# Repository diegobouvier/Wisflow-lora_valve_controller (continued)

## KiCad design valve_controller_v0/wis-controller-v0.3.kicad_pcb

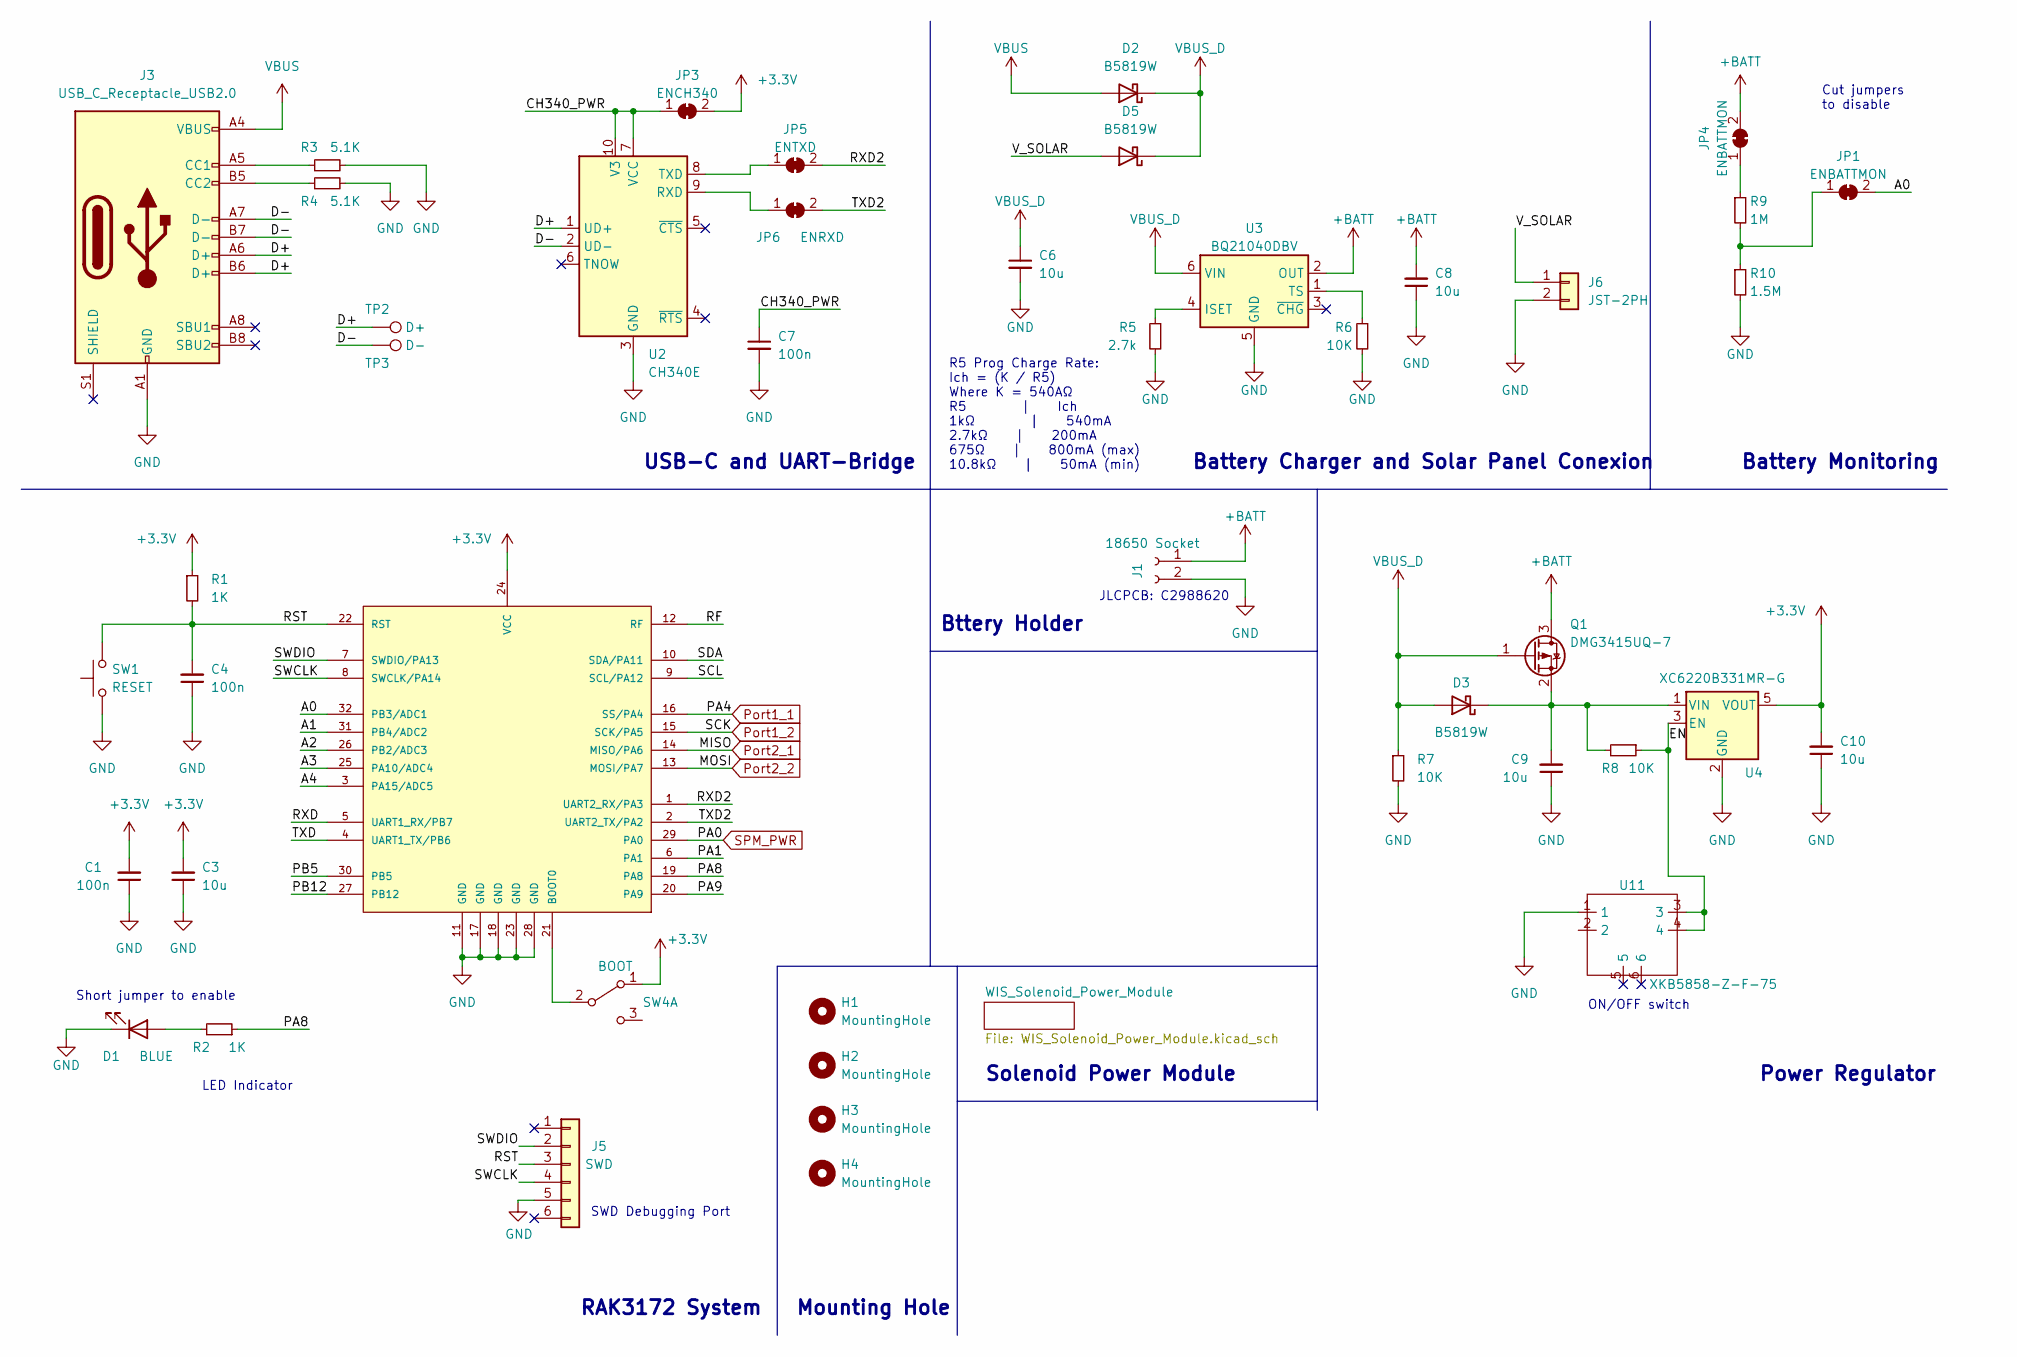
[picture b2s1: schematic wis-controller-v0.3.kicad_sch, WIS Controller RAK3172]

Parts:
C1, C4, C7: 100n; C_0603_1608Metric; Part Description Ceramic Capacitor 100nF 10% 10V X7R
C3, C6: 10u; C_0603_1608Metric; Part Description Ceramic Capacitor 10uF 10% 10V X5R
C8, C9, C10: 10u; C_0805_2012Metric; Part Description Ceramic Capacitor 10uF 10% 10V X5R
D1: BLUE; LED_0603_1608Metric; Part Description Blue 2V 25mA
D2, D5: B5819W; D_SOD-123
D3: B5819W; D_SOD-123; Part Description 0.05mA@40V 0.58V@1A
H1, H2, H3, H4: MountingHole; MountingHole_2.5mm
J1: 18650 Socket; BatteryHolder_MPD_BK-18650-PC2
J3: USB_C_Receptacle_USB2.0; USB_C_Receptacle_XKB_U262-16XN-4BVC11; Part Number U262-161N-4BVC11
J5: SWD; Tag-Connect_TC2030-IDC-NL_2x03_P1.27mm_Vertical
J6: JST-2PH; JST_PH_S2B-PH-SM4-TB_1x02-1MP_P2.00mm_Horizontal; Part Number JST-PH S2B-PH-SM4-TB
JP1, JP4: ENBATTMON; SolderJumper-2_P1.3mm_Bridged_RoundedPad1.0x1.5mm
JP3: ENCH340; SolderJumper-2_P1.3mm_Bridged_RoundedPad1.0x1.5mm
JP5: ENTXD; SolderJumper-2_P1.3mm_Bridged_RoundedPad1.0x1.5mm
JP6: ENRXD; SolderJumper-2_P1.3mm_Bridged_RoundedPad1.0x1.5mm
Q1: DMG3415UQ-7; SOT-23; Part Number DMG3415UQ-7
R1, R2: 1K; R_0603_1608Metric; Part Description Resistor 1k 5% 100mW
R3, R4: 5.1K; R_0603_1608Metric; Part Description Resistor 5.1K 1% 100mW
R5: 2.7k; R_0603_1608Metric; Part Description Resistor 5.1k 1% 100mW
R6, R7, R8: 10K; R_0603_1608Metric; Part Description Resistor 10k 5% 100mW
R9: 1M; R_0603_1608Metric; Part Description Resistor 4.7M 1% 100mW
R10: 1.5M; R_0603_1608Metric; Part Description Resistor 10M 1% 100mW
SW1: RESET; SW_SPST_B3U-1000P; Part Number B3U-1000P
SW4: BOOT; Slide_switch
TP2: D+; TestPoint_Pad_D1.0mm
TP3: D-; TestPoint_Pad_D1.0mm
U1: RAK3172; Part Number RAK3172
U2: CH340E; MSOP-10_3x3mm_P0.5mm; Part Number CH340E
U3: BQ21040DBV; SOT-23-6
U4: XC6220B331MR-G; SOT-23-5; Part Number XC6220B331MR-G
U11: XKB5858-Z-F-75; WIS-Push_Button

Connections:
+3.3V: C1.2, C3.2, C10.2, JP3.2 (B), R1.1, SW4.1 (A), U1.24 (VCC), U4.5 (VOUT); also elsewhere on the board
+BATT: C8.2, J1.1, JP4.2 (B), Q1.3 (D), U3.2 (OUT); also elsewhere on the board
/A0: JP1.2 (B), U1.32 (PB3/ADC1)
/A1: U1.31 (PB4/ADC2)
/A2: U1.26 (PB2/ADC3)
/A3: U1.25 (PA10/ADC4)
/A4: U1.3 (PA15/ADC5)
/CH340_PWR: C7.1, JP3.1 (A), U2.7 (VCC), U2.10 (V3)
/D+: J3.A6 (D+), J3.B6 (D+), TP2.1, U2.1 (UD+)
/D-: J3.A7 (D-), J3.B7 (D-), TP3.1, U2.2 (UD-)
/EN: R8.1, U4.3 (EN), U11.3, U11.4
/PA1: U1.6 (PA1)
/PA8: R2.1, U1.19 (PA8)
/PA9: U1.20 (PA9)
/PB5: U1.30 (PB5)
/PB12: U1.27 (PB12)
/RF: U1.12 (RF)
/RST: C4.2, J5.3, R1.2, SW1.2, U1.22 (RST)
/RXD: U1.5 (UART1_RX/PB7)
/RXD2: JP5.2 (B), U1.1 (UART2_RX/PA3)
/SCL: U1.9 (SCL/PA12)
/SDA: U1.10 (SDA/PA11)
/SWCLK: J5.4, U1.8 (SWCLK/PA14)
/SWDIO: J5.2, U1.7 (SWDIO/PA13)
/TXD: U1.4 (UART1_TX/PB6)
/TXD2: JP6.2 (B), U1.2 (UART2_TX/PA2)
/V_SOLAR: D5.2 (A), J6.1
GND: C1.1, C3.1, C4.1, C6.2, C7.2, C8.1, C9.1, C10.1, D1.1 (K), J1.2, J3.A1 (GND), J3.A12 (GND), J3.B1 (GND), J3.B12 (GND), J5.5, J6.2, R3.2, R4.2, R5.2, R6.2, R7.2, R10.2, SW1.1, U1.11 (GND), U1.17 (GND), U1.18 (GND), U1.23 (GND), U1.28 (GND), U2.3 (GND), U3.5 (GND), U4.2 (GND), U11.1; also elsewhere on the board
unnamed: D1.2 (A), R2.2
unnamed: C9.2, D3.1 (K), Q1.2 (S), R8.2, U4.1 (VIN)
unnamed: J3.A5 (CC1), R3.1
unnamed: J3.B5 (CC2), R4.1
unnamed: JP1.1 (A), R9.2, R10.1
unnamed: JP4.1 (A), R9.1
unnamed: JP5.1 (A), U2.8 (TXD)
unnamed: JP6.1 (A), U2.9 (RXD)
unnamed: SW4.2 (B), U1.21 (BOOT0)
unnamed: R5.1, U3.4 (ISET)
unnamed: R6.1, U3.1 (TS)
Port1_1: U1.16 (SS/PA4); also elsewhere on the board
Port1_2: U1.15 (SCK/PA5); also elsewhere on the board
Port2_1: U1.14 (MISO/PA6); also elsewhere on the board
Port2_2: U1.13 (MOSI/PA7); also elsewhere on the board
SPM_PWR: U1.29 (PA0); also elsewhere on the board
VBUS: D2.2 (A), J3.A4 (VBUS), J3.A9 (VBUS), J3.B4 (VBUS), J3.B9 (VBUS)
VBUS_D: C6.1, D2.1 (K), D3.2 (A), D5.1 (K), Q1.1 (G), R7.1, U3.6 (VIN)

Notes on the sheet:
ON/OFF switch
Battery Monitoring
RAK3172 System
Mounting Hole
R5 Prog Charge Rate: Ich = (K / R5) Where K = 540AΩ R5 | Ich 1kΩ | 540mA 2.7kΩ | 200mA 675Ω | 800mA (max) 10.8kΩ | 50mA (min)
Cut jumpers to disable
JLCPCB: C2988620
Short jumper to enable
USB-C and UART-Bridge
SWD Debugging Port
LED Indicator
Solenoid Power Module
Power Regulator
Battery Charger and Solar Panel Conexion
Bttery Holder

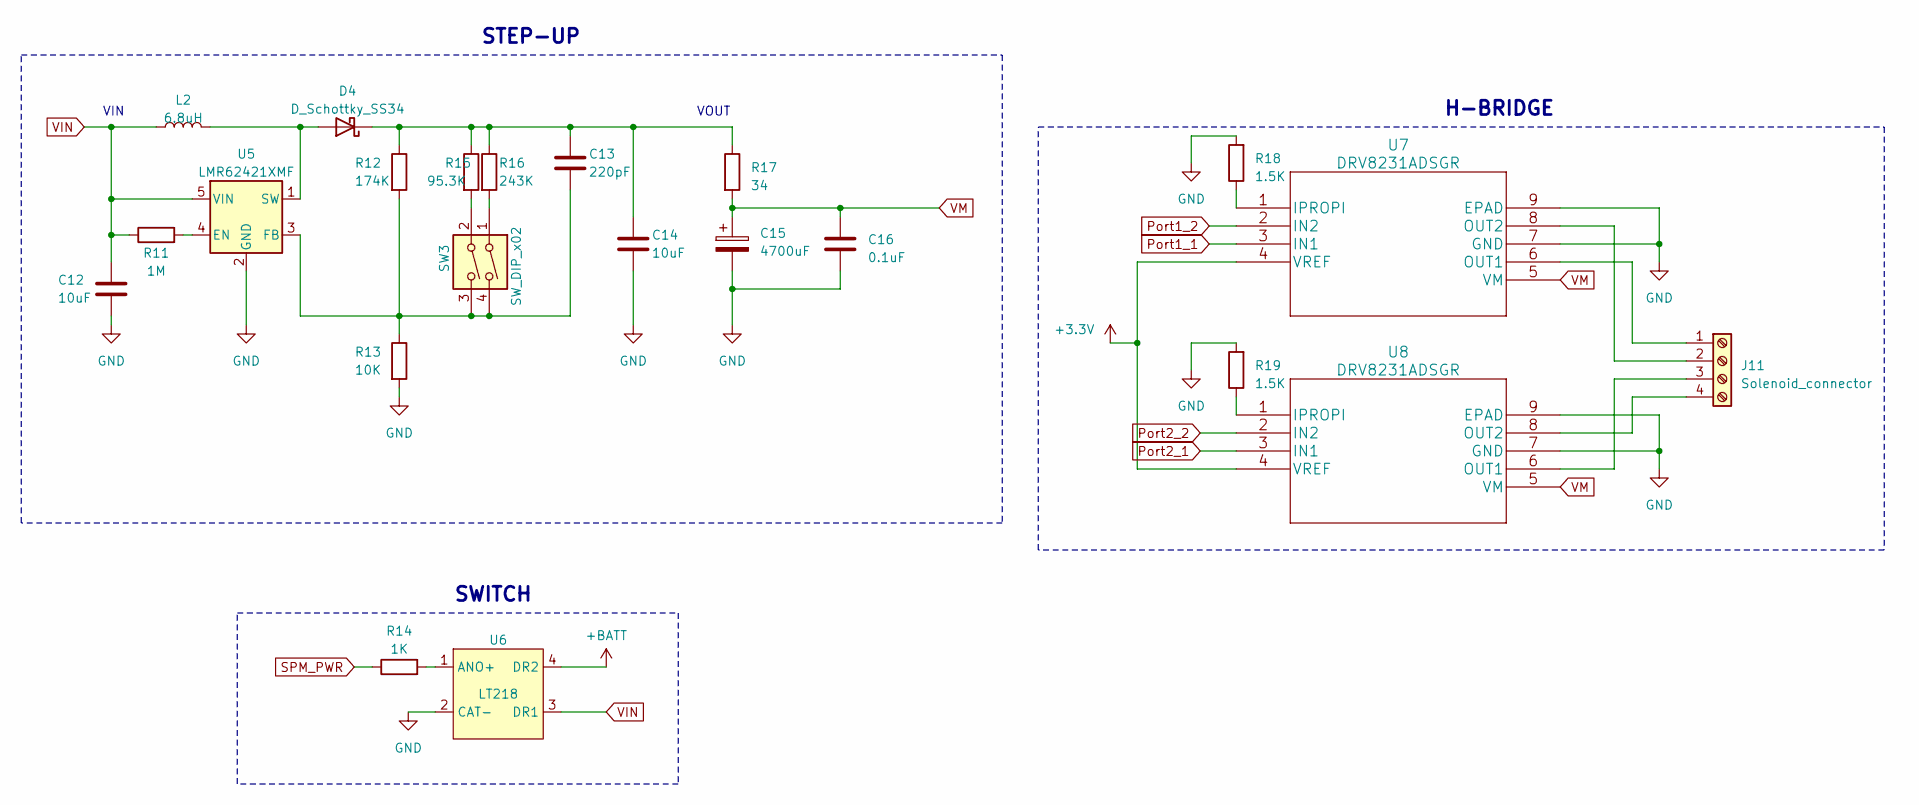
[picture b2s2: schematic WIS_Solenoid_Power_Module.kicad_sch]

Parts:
C12, C14: 10uF; C_0603_1608Metric
C13: 220pF; C_0603_1608Metric
C15: 4700uF; CP_Radial_D16.0mm_P7.50mm
C16: 0.1uF; C_0603_1608Metric
D4: D_Schottky_SS34; Dioide_v1.4
J11: Solenoid_connector; TerminalBlock_bornier-4_P5.08mm
L2: 6.8uH; Inductor_6R8
R11: 1M; R_0603_1608Metric
R12: 174K; R_0603_1608Metric
R13: 10K; R_0603_1608Metric
R14: 1K; R_0603_1608Metric
R15: 95.3K; R_0603_1608Metric
R16: 243K; R_0603_1608Metric
R17: 34; R_2512_6332Metric
R18, R19: 1.5K; R_0603_1608Metric
SW3: SW_DIP_x02; WIS_DIP_Switch
U5: LMR62421XMF; SOT-23-5
U6: LT218; SOP-4
U7, U8: DRV8231ADSGR

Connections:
+3.3V: U7.4 (VREF), U8.4 (VREF); also elsewhere on the board
+BATT: U6.4 (DR2); also elsewhere on the board
GND: C12.2, C14.2, C15.2, C16.2, R13.2, R18.2, R19.2, U5.2 (GND), U6.2 (CAT-), U7.7 (GND), U7.9 (EPAD), U8.7 (GND), U8.9 (EPAD); also elsewhere on the board
unnamed: D4.2 (A), L2.2, U5.1 (SW)
unnamed: C13.1, C14.1, D4.1 (K), R12.1, R15.1, R16.1, R17.1
unnamed: J11.1, U7.6 (OUT1)
unnamed: J11.2, U7.8 (OUT2)
unnamed: J11.3, U8.6 (OUT1)
unnamed: J11.4, U8.8 (OUT2)
unnamed: R15.2, SW3.2
unnamed: R16.2, SW3.1
unnamed: R11.2, U5.4 (EN)
unnamed: C13.2, R12.2, R13.1, SW3.3, SW3.4, U5.3 (FB)
unnamed: R14.2, U6.1 (ANO+)
unnamed: R18.1, U7.1 (IPROPI)
unnamed: R19.1, U8.1 (IPROPI)
Port1_1: U7.3 (IN1); also elsewhere on the board
Port1_2: U7.2 (IN2); also elsewhere on the board
Port2_1: U8.3 (IN1); also elsewhere on the board
Port2_2: U8.2 (IN2); also elsewhere on the board
SPM_PWR: R14.1; also elsewhere on the board
VIN: C12.1, L2.1, R11.1, U5.5 (VIN), U6.3 (DR1)
VM: C15.1, C16.1, R17.2, U7.5 (VM), U8.5 (VM)

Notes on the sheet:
H-BRIDGE
STEP-UP
SWITCH
VOUT
VIN

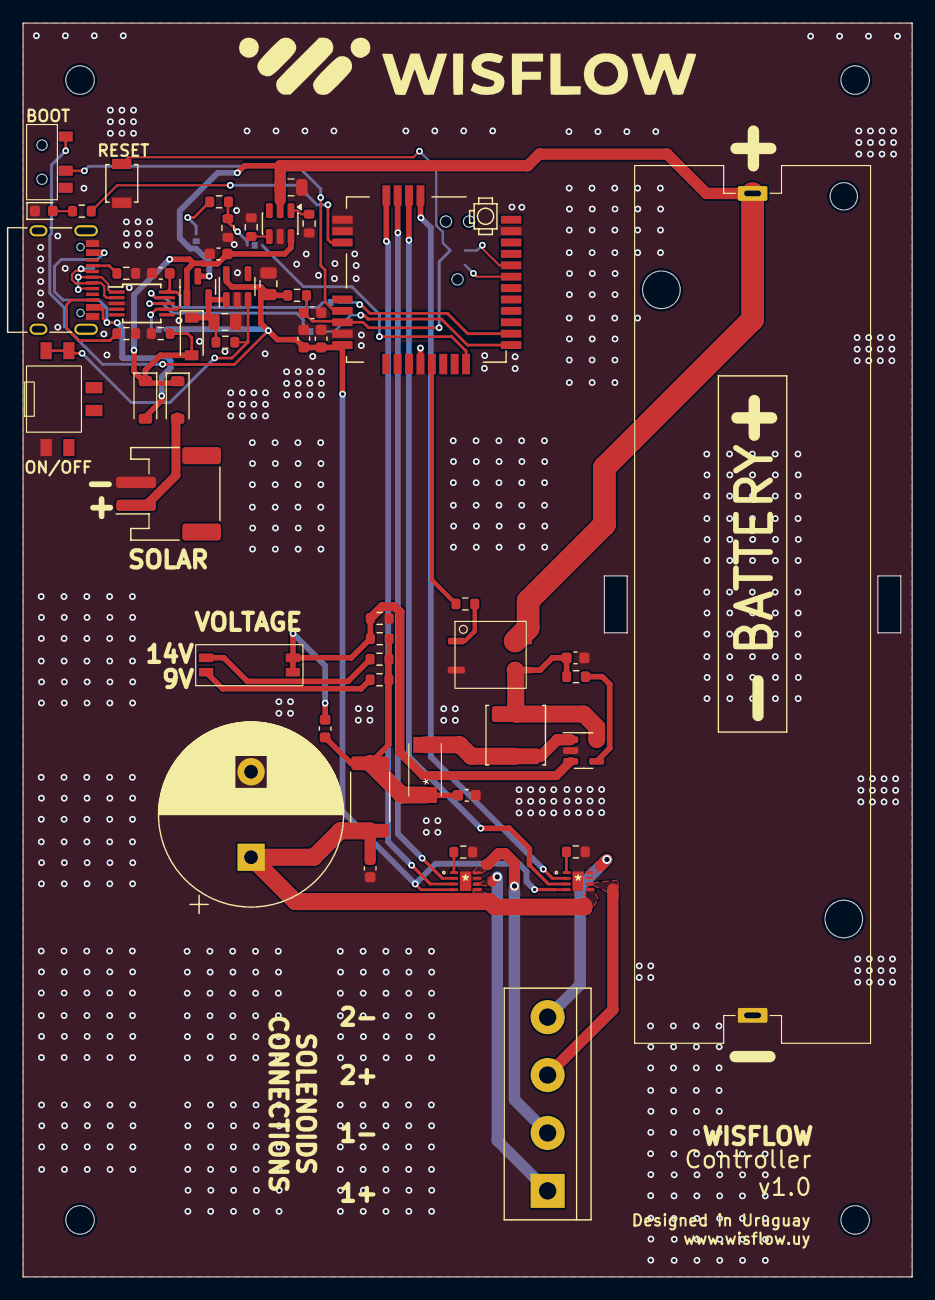
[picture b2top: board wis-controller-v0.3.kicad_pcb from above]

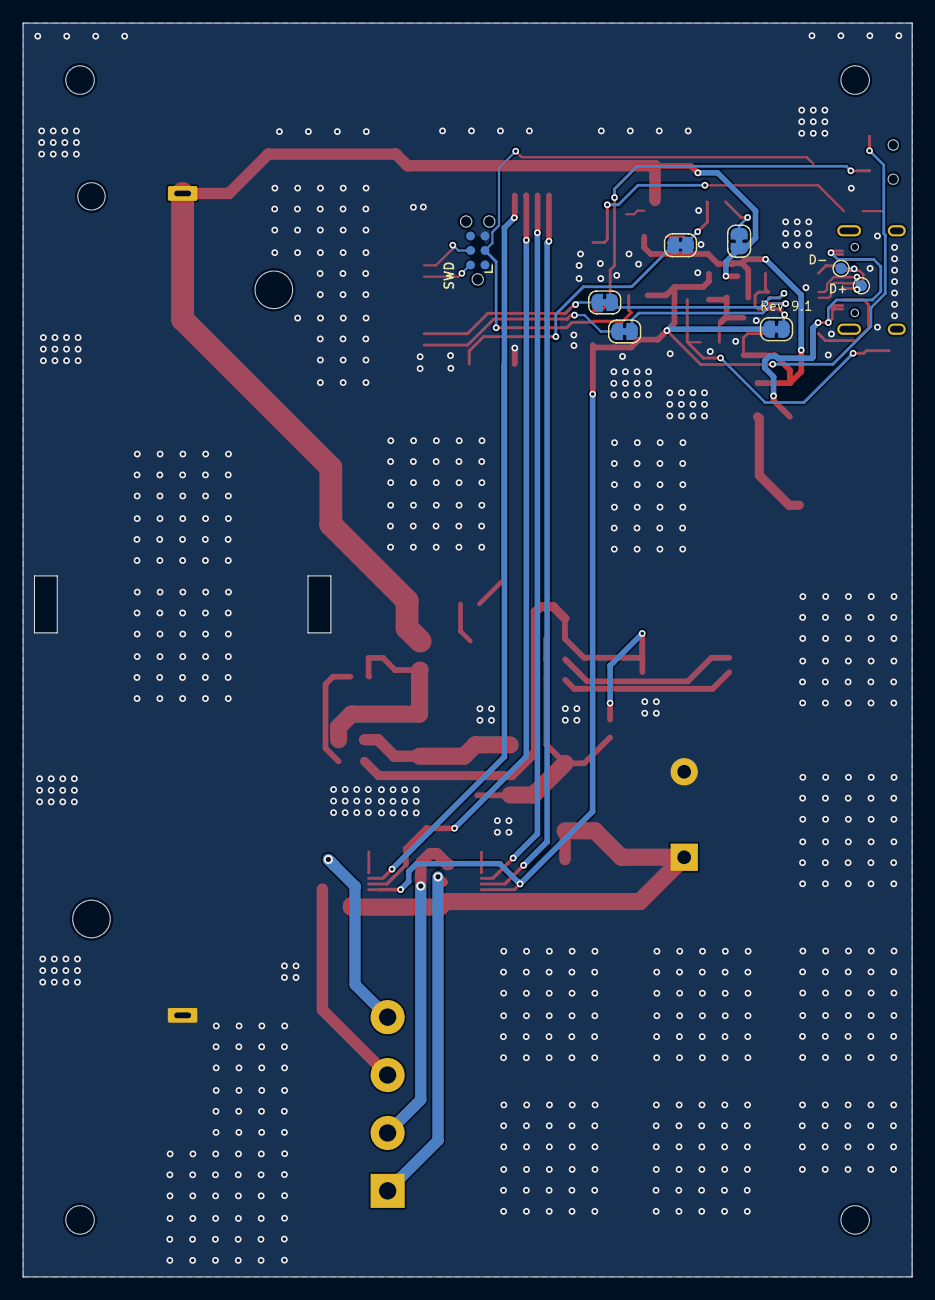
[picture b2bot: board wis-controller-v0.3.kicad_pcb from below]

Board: 2 copper layers, 78.0 x 110.0 mm, 67 parts (8 on the bottom side), 48 nets.

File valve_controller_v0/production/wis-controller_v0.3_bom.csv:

Designator,Footprint,Quantity,Value,LCSC Part #
"C1, C4, C7",0603,3,100n,
"C10, C8, C9",0805,3,10u,
"C12, C14",0603,2,10uF,
C13,0603,1,220pF,
C15,CP_Radial_D16.0mm_P7.50mm,1,4700uF,
C16,0603,1,0.1uF,
"C3, C6",0603,2,10u,
D1,0603,1,BLUE,
"D2, D3, D5",D_SOD-123,3,B5819W,
D4,Dioide_v1.4,1,D_Schottky_SS34,
"H1, H2, H3, H4",MountingHole_2.5mm,4,MountingHole,
J1,18650_SMD,1,18650 Socket,
J11,TerminalBlock_bornier-4_P5.08mm,1,Solenoid_connector,
J3,USB_C_Receptacle_XKB_U262-16XN-4BVC11,1,USB_C_Receptacle_USB2.0,
J5,Tag-Connect_TC2030-IDC-NL_2x03_P1.27mm_Vertical,1,SWD,
J6,JST_PH_S2B-PH-SM4-TB_1x02-1MP_P2.00mm_Horizontal,1,JST-2PH,
"JP1, JP4",SolderJumper-2_P1.3mm_Bridged_RoundedPad1.0x1.5mm,2,ENBATTMON,
JP3,SolderJumper-2_P1.3mm_Bridged_RoundedPad1.0x1.5mm,1,ENCH340,
JP5,SolderJumper-2_P1.3mm_Bridged_RoundedPad1.0x1.5mm,1,ENTXD,
JP6,SolderJumper-2_P1.3mm_Bridged_RoundedPad1.0x1.5mm,1,ENRXD,
L2,Inductor_6R8,1,6.8uH,
Q1,SOT-23,1,DMG3415UQ-7,
"R1, R14, R2",0603,3,1K,
R10,0603,1,1.5M,
"R11, R9",0603,2,1M,
R12,0603,1,174K,
"R13, R6, R7, R8",0603,4,10K,
R15,0603,1,95.3K,
R16,0603,1,243K,
R17,2512,1,34,
"R18, R19",0603,2,1.5K,
"R3, R4",0603,2,5.1K,
R5,0603,1,2.7k,
SW1,SW_SPST_B3U-1000P,1,RESET,
SW3,WIS_DIP_Switch,1,SW_DIP_x02,
SW4,Slide_switch,1,BOOT,
TP2,TestPoint_Pad_D1.0mm,1,D+,
TP3,TestPoint_Pad_D1.0mm,1,D-,
U1,RAK3172,1,RAK3172,
U11,WIS-Push_Button,1,XKB5858-Z-F-75,
U2,MSOP-10_3x3mm_P0.5mm,1,CH340E,
U3,SOT-23-6,1,BQ21040DBV,
U4,SOT-23-5,1,XC6220B331MR-G,
U5,SOT-23-5,1,LMR62421XMF,
U6,SOP-4,1,LT218,
"U7, U8",DRV8231ADSGR,2,DRV8231ADSGR,

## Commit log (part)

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2026-03-24 Add v0 of the PCB
    Added the original version of hte PCB to the repository
2026-03-26 Replaced battery charger and battery holder
    - Replaced battery charger to support the new solar panel
    - Replaced the battery holder by a plastic enclosure one
    - Reconnected the on/off switch to avoid putting EN pin floating temporarly whne swithced
2026-03-26 Uniformized D2,D3 and D5
    - Selected the same partnumber forD2, D3 and D5, all of the 1A and 40V.
2026-03-26 Removed most of user comments measurements
2026-04-06 Solenoid terminal block relocated
2026-04-14 Updated v0.3 for fabrication
    - Removed unnecesary via in U11 pad2
    - Solved courtyard overlaping of J3-D1, J3-R2, U1-C4 and U1-C1
    - Removed silkscreen for R6 and U3
    - Generated manufacturing files (production folder)
2026-04-16 Updated BOM according to manufacturing
    Downloaded the final BOM after components selection in JLCPCB
2026-04-18 Updated the 18650 battery holder
    Changed the battery holder for the 18650 battery. Created new footprint and updated the PCB layout. Added cutouts for zip-ties
2026-04-18 Updated the PCB order design
    Updated the PCB order files. Created v0.3b and updated v0.3 files
2026-04-19 Corected the location of the solenoid connector
    Reverted the modification of the solenoid connector to maintain its original position
2026-05-26 Modified location of silkscreen
    Modified the location of the silkscreen to avoid being covered by the output connector
2026-06-03 Corrected inductor L2 footprint
    The footprint of L2 was incorrect and JLCPCB rejected to solder it (The same design was already manufactured before)
2026-06-03 First version of the new schematic
    Redo the entire schematic from scratch
    Added battery shutdown measurement circuit (In the previous design the measuring circuit is always on)
    Added LT218, Switch and DRV8845 tothe Wisflow Symbol library
2026-06-23 Finished first version of the schematic
    Added hierarchical sheets for every block (Power, USB, Valve Drivers, MCU, Step Up)
    Updated the battery voltage measurement circuit
    Assigned footprint for most of the components (Work in Progress)
    Placed most of the components near related main active components
2026-06-24 Assigned footprints
    Assigned footprints
    Selected JLCPCB part numbers and searched for alternatives for some components (diodes, transistors)
    Imported previos footprint library
2026-06-25 Basic routing (block level)
    Creation of switches footprint
    Definition of manufacturing rules
    Basic floorplan and layout (routing) of every block
2026-06-25 Corrected power switch footprint
    Corrected the footprint (numbering of the pins) according to the EasyEDA footprint model on JLCPCB
    Reviewed the boot select footprint pin assignment also
